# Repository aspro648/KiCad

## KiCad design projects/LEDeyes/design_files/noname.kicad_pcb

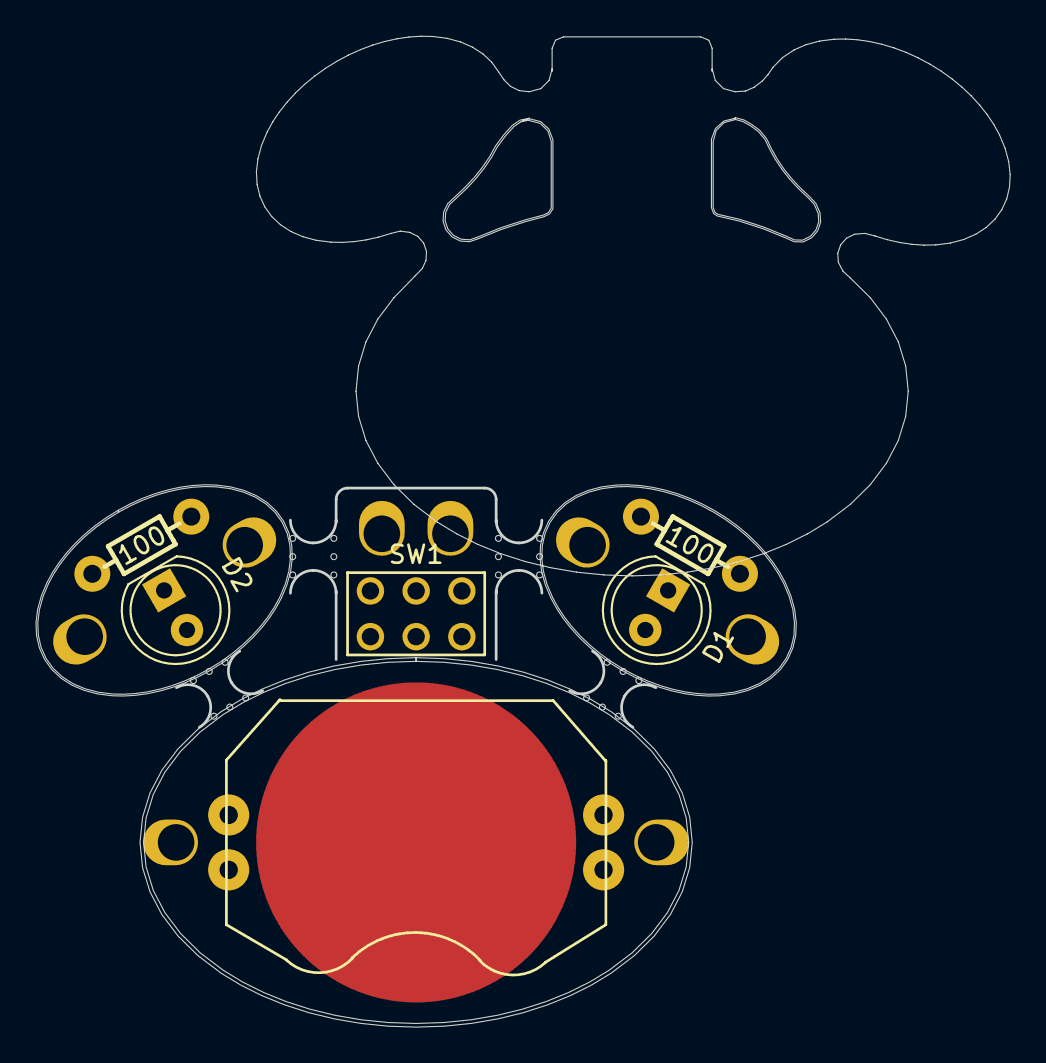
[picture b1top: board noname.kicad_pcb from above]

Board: 2 copper layers, 54.1 x 55.0 mm, 22 parts (0 on the bottom side), 5 nets.

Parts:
B3, B3#2, B3#3, B3#4: 1pin; MOUSEBITEx3_edges
BT1: Battery_Cell; BATT_CR2032
D1, D2: LED; LED_D5.0mm
J1, J2, J3, J4, J5, J6, J7, J8: CONN_01X01; SEWPAD
R1, R2: 100; Resistor_Horz
SW1: SW_SPST; mySwitchDPDT
svg2mod, svg2mod#2, svg2mod#3: G***; elipse
svg2mod#4: G***; edge_cuts2

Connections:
unnamed: BT1.1, J6.1, SW1.2
unnamed: BT1.2, J1.1, J2.1, J3.1, J8.1, R1.2, R2.2
unnamed: D1.1, R1.1
unnamed: D1.2, D2.2, J4.1, J5.1, J7.1, SW1.1
unnamed: D2.1, R2.1

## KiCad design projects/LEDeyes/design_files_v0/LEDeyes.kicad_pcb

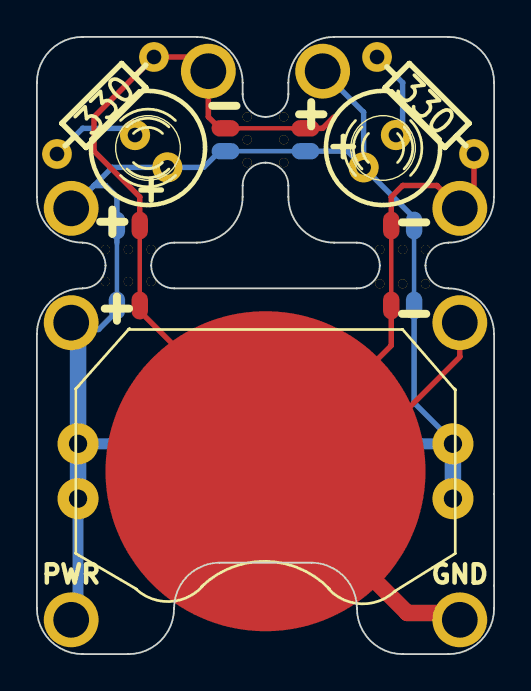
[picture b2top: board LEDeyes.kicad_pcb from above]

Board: 2 copper layers, 25.4 x 34.3 mm, 21 parts (0 on the bottom side), 4 nets.

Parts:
BT1: BATTERY; BATT_CR2032
B_N1, B_N2: GND; 1pin-Sew-thin
B_P1, B_P2: PWR; 1pin-Sew-thin
D1, D2: LED; LED-5MM
L1, L1_C1, L1_C2, L2: 1pin-Sew-thin
R1, R2: 330; R3-LARGE_PADS
VAL: MadeInOregonRev25
VAL#2: MB225rev
p: P; 3hole_mousebite
p#2, p#3, p#4, p#5, p#6: P; 3hole_mousebite

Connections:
GND: BT1.2, B_N1.1, B_N2.1, L1_C1.1, L2.1, R1.1, R2.1
unnamed: BT1.1, B_P1.1, B_P2.1, D1.1, D2.1, L1.1, L1_C2.1
unnamed: D2.2, R2.2
unnamed: D1.2, R1.2

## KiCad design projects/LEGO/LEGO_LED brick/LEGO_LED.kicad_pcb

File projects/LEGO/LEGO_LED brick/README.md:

Lighting Brick for Lego

Bill Of Materials
----------------
  
- 1 ea., Perfect Purple PCB from OSH Park, with not so perfect layout from design_files/project.kicad_pcb file.
- 8 ea., 1206 or 0805 LED with wide viewing angle:
	- LED WL-SWTP COOL WHT 6000K 1206, Vf 3.0 https://www.digikey.com/short/zzt3mq
- 8 ea., 0805 resistor to match forward voltage of LED
	- RES SMD 100 OHM 5% 1/8W 0805, https://www.digikey.com/short/z7nv19
- 1 ea., X3, CONN RCPT MICRO USB R/A SMD, Molex 1050170001, https://www.digikey.com/short/jb2205

Connectors and jumpers as needed:
- X ea., 2POS Picoblade vertical header, https://www.digikey.com/short/p9twrj
- 1 ea., CONN HEADER R/A 2POS 1.25MM, https://www.digikey.com/short/p5r2dn
- X ea., 2POS PicoBlade housing, https://www.digikey.com/short/p4wz0d
- X ea., 12" PRE-CRIMP 1852 RED, https://www.digikey.com/short/pbfbnb
- X ea., 12" PRE-CRIMP 1852 BLACK, https://www.digikey.com/short/pbfbnd

License
----------------
[Attribution-ShareAlike 3.0 United States (CC BY-SA 3.0 US)](https://creativecommons.org/licenses/by-sa/3.0/us/)

You are free to:

- Share — copy and redistribute the material in any medium or format
- Adapt — remix, transform, and build upon the material

Under the following terms:

- Attribution — You must give appropriate credit, provide a link to the license, and indicate if changes were made. You may do so in any reasonable manner, but not in any way that suggests the licensor endorses you or your use.
- ShareAlike — If you remix, transform, or build upon the material, you must distribute your contributions under the same license as the original.

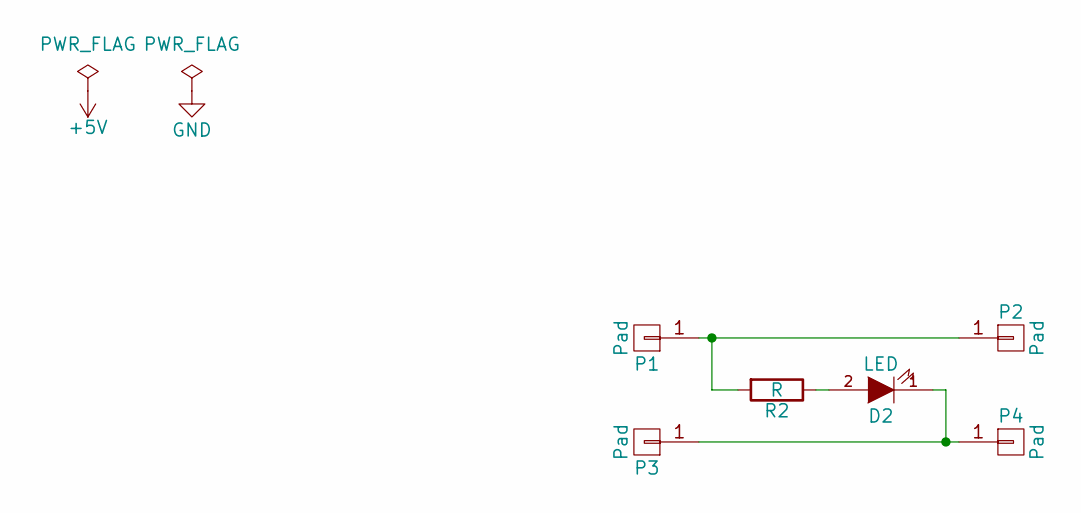
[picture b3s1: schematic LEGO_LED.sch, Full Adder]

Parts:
D2: LED; LED_0805
P1, P2, P3, P4: Pad; Pin_Header_Straight_1x01_Pitch2.00mm
R2: R; R_0805

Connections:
unnamed: D2.1 (K), P3.1, P4.1
unnamed: D2.2 (A), R2.1
unnamed: P1.1, P2.1, R2.2

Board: 2 copper layers, 6 parts (0 on the bottom side), 3 nets, no tracks yet.

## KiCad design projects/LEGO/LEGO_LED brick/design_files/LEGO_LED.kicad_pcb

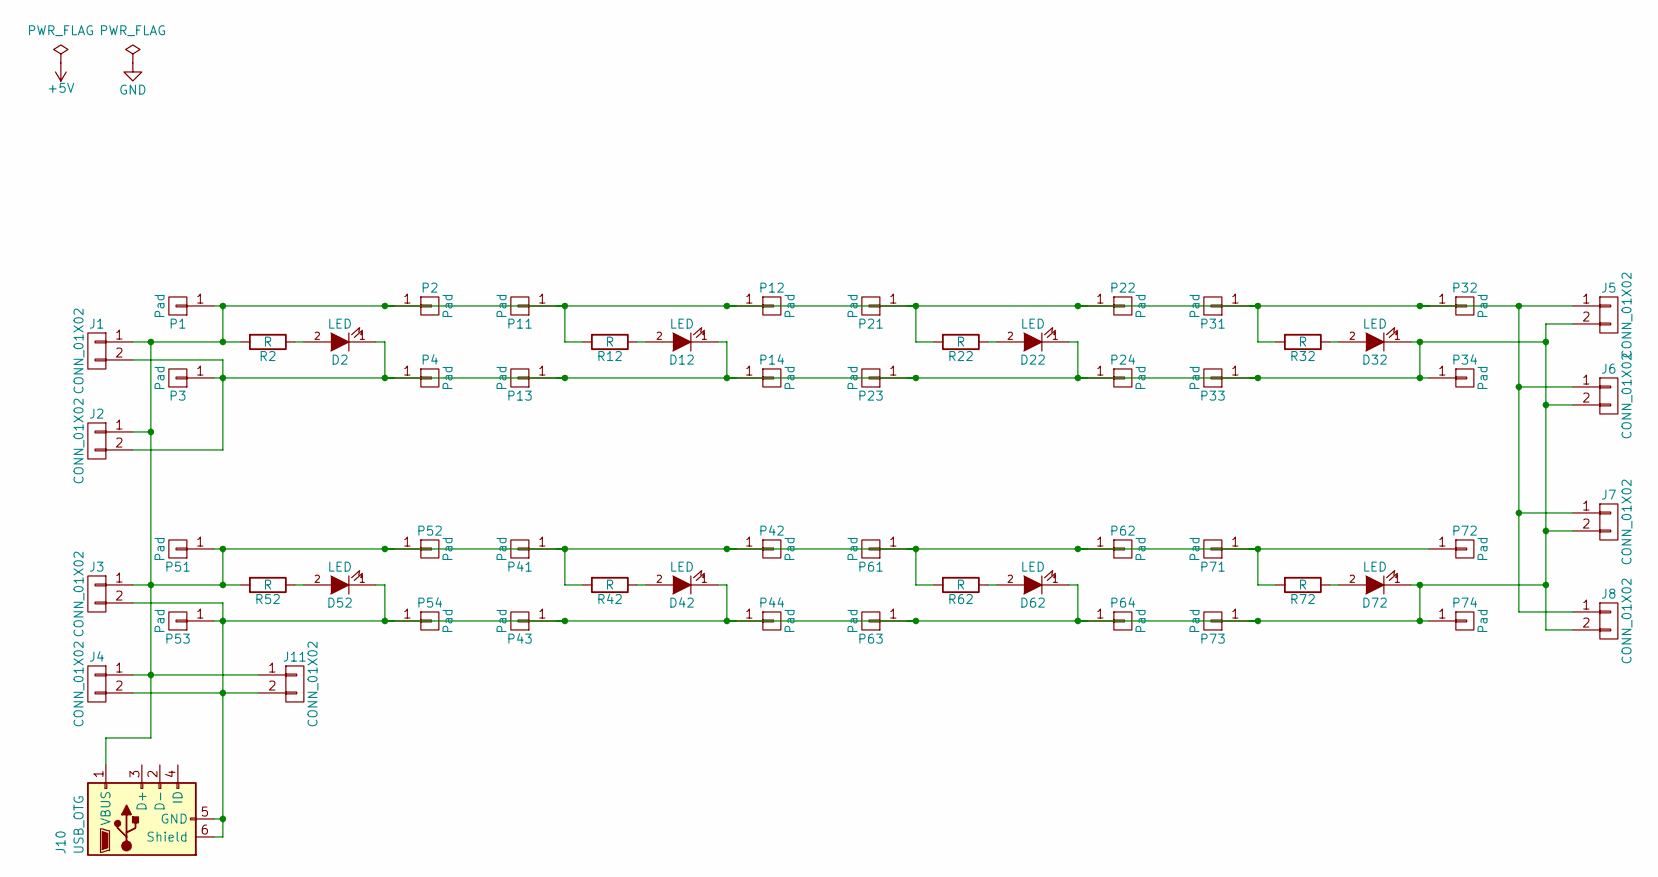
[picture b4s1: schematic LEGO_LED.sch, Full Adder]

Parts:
D2, D12, D22, D32, D42, D52, D62, D72: LED; LED_0805
J1, J2, J3, J4, J5, J6, J7, J8, J11: CONN_01X02; Molex_PicoBlade_53047-0210_02x1.25mm_Straight
J10: USB_OTG
P1, P2, P3, P4, P11, P12, P13, P14, P21, P22, P23, P24, P31, P32, P33, P34, P41, P42, P43, P44, P51, P52, P53, P54, P61, P62, P63, P64, P71, P72, P73, P74: Pad; Pin_Header_Straight_1x01_Pitch2.00mm
R2, R12, R22, R32, R42, R52, R62, R72: R; R_0805

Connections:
unnamed: D2.2 (A), R2.1
unnamed: D2.1 (K), D12.1 (K), D22.1 (K), D32.1 (K), D42.1 (K), D52.1 (K), D62.1 (K), D72.1 (K), J1.2, J2.2, J3.2, J4.2, J5.2, J6.2, J7.2, J8.2, J10.5 (GND), J10.6 (Shield), J11.2, P3.1, P4.1, P13.1, P14.1, P23.1, P24.1, P33.1, P34.1, P43.1, P44.1, P53.1, P54.1, P63.1, P64.1, P73.1, P74.1
unnamed: D12.2 (A), R12.1
unnamed: D22.2 (A), R22.1
unnamed: D32.2 (A), R32.1
unnamed: D42.2 (A), R42.1
unnamed: D52.2 (A), R52.1
unnamed: D62.2 (A), R62.1
unnamed: D72.2 (A), R72.1
unnamed: J1.1, J2.1, J3.1, J4.1, J5.1, J6.1, J7.1, J8.1, J10.1 (VBUS), J11.1, P1.1, P2.1, P11.1, P12.1, P21.1, P22.1, P31.1, P32.1, P41.1, P42.1, P51.1, P52.1, P61.1, P62.1, P71.1, P72.1, R2.2, R12.2, R22.2, R32.2, R42.2, R52.2, R62.2, R72.2

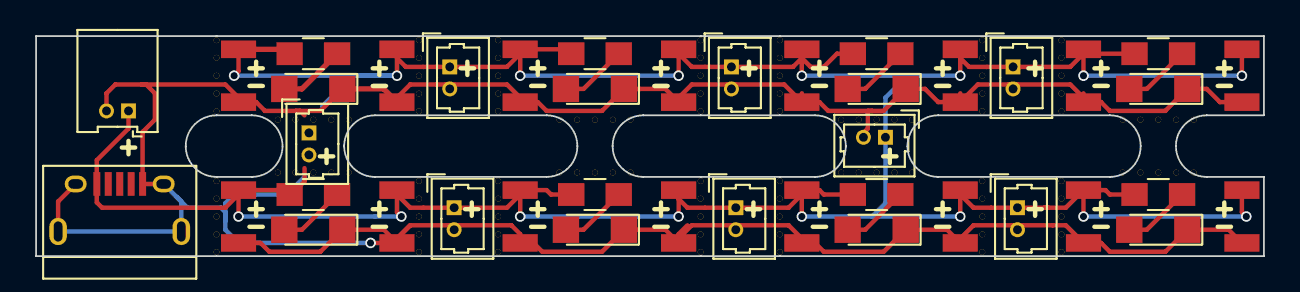
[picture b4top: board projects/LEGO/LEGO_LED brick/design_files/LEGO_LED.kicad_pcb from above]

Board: 2 copper layers, 69.8 x 12.5 mm, 58 parts (0 on the bottom side), 10 nets.
